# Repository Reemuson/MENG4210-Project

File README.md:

<h1 align="center">DREAM</h1>

<h2 align="center">Data Recording and Electrophysiological Acquisition Module</h2>

<p align="center" width="100%">
  
</p>

***

<p align="center">
  
&nbsp; &nbsp; &nbsp; &nbsp;
  
</p>

***

## SPECIFICATIONS

| Parameter | Value | 
| --- | --- |
| Dimensions | 100.0 × 60.0 mm |

***

## DIRECTORY STRUCTURE

    .
    ├─ Computations       # Misc calculations
    ├─ HTML               # HTML files for generated webpage
    ├─ Images             # Pictures and renders
    │
    ├─ kibot_resources    # External resources for KiBot
    │  ├─ colors          # Color theme for KiCad
    │  ├─ fonts           # Fonts used in the project
    │  ├─ scripts         # External scripts used with KiBot
    │  └─ templates       # Templates for KiBot generated reports
    │
    ├─ kibot_yaml         # KiBot YAML config files
    ├─ KiRI               # KiRI (PCB diff viewer) files
    │
    ├─ lib                # KiCad footprint and symbol libraries
    │  ├─ 3d_models       # Component 3D models
    │  ├─ lib_fp          # Footprint libraries
    │  └─ lib_sym         # Symbol libraries
    │
    ├─ Logos              # Logos
    │
    ├─ Manufacturing      # Assembly and fabrication documents
    │  ├─ Assembly        # Assembly documents (BoM, pos, notes)
    │  │
    │  └─ Fabrication     # Fabrication documents (ZIP, notes)
    │     ├─ Drill Tables # CSV drill tables
    │     └─ Gerbers      # Gerbers
    │
    ├─ Report             # Reports for ERC/DRC
    ├─ Schematic          # PDF of schematic
    ├─ Templates          # Title block templates
    ├─ Testing
    │  └─ Testpoints      # Testpoints tables      
    │
    └─ Variants           # Outputs for assembly variants

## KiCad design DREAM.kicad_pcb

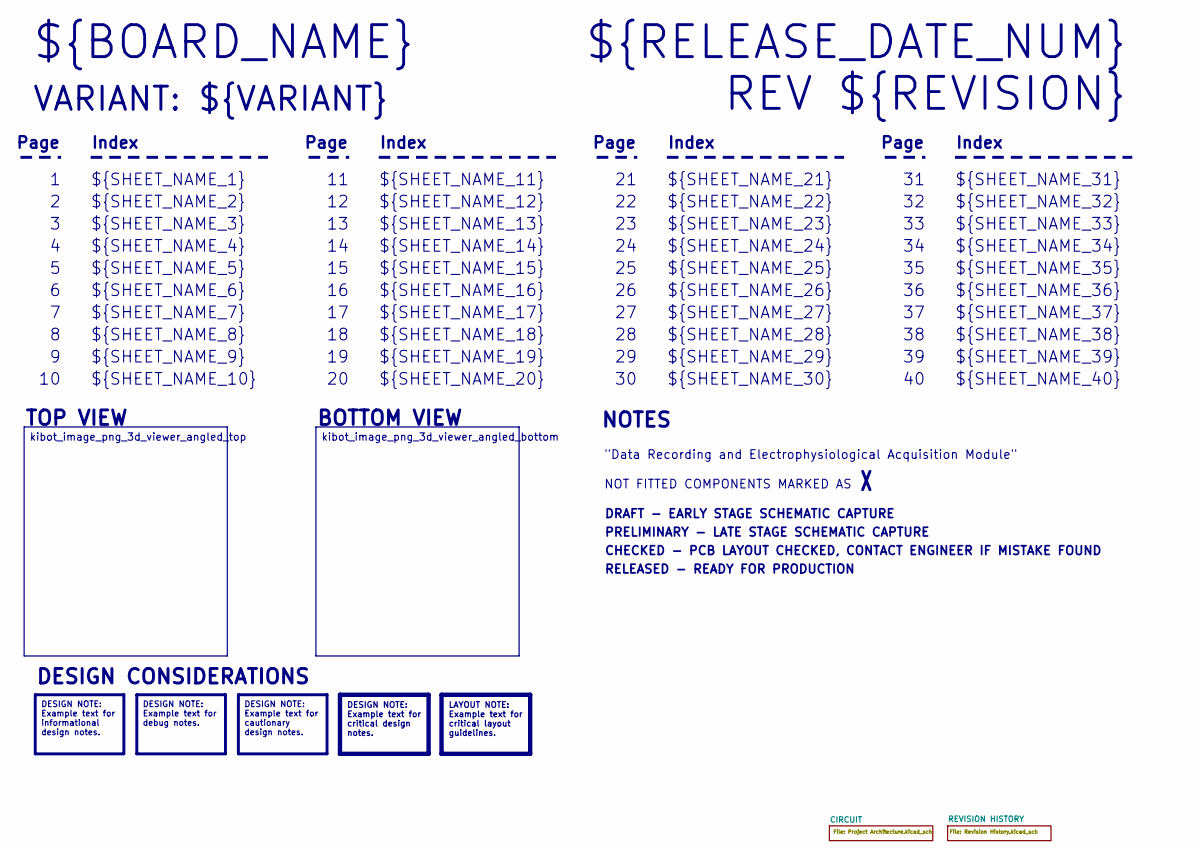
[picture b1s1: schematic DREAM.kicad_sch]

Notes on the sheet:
VARIANT: ${VARIANT}
RELEASED - READY FOR PRODUCTION
${SHEET_NAME_24}
Index
Page
PRELIMINARY - LATE STAGE SCHEMATIC CAPTURE
${SHEET_NAME_22}
DRAFT - EARLY STAGE SCHEMATIC CAPTURE
${SHEET_NAME_12}
${SHEET_NAME_8}
${SHEET_NAME_2}
${SHEET_NAME_5}
${SHEET_NAME_20}
${SHEET_NAME_23}
${RELEASE_DATE_NUM}
${SHEET_NAME_35}
NOT FITTED COMPONENTS MARKED AS
${SHEET_NAME_11}
${SHEET_NAME_6}
${SHEET_NAME_37}
${SHEET_NAME_26}
${SHEET_NAME_36}
REV ${REVISION}
${SHEET_NAME_15}
CHECKED - PCB LAYOUT CHECKED, CONTACT ENGINEER IF MISTAKE FOUND
BOTTOM VIEW
${SHEET_NAME_14}
${SHEET_NAME_21}
${SHEET_NAME_17}
${SHEET_NAME_18}
${SHEET_NAME_7}
${SHEET_NAME_31}
${BOARD_NAME}
NOTES
${SHEET_NAME_40}
${SHEET_NAME_39}
${SHEET_NAME_32}
${SHEET_NAME_1}
${SHEET_NAME_9}
${SHEET_NAME_38}

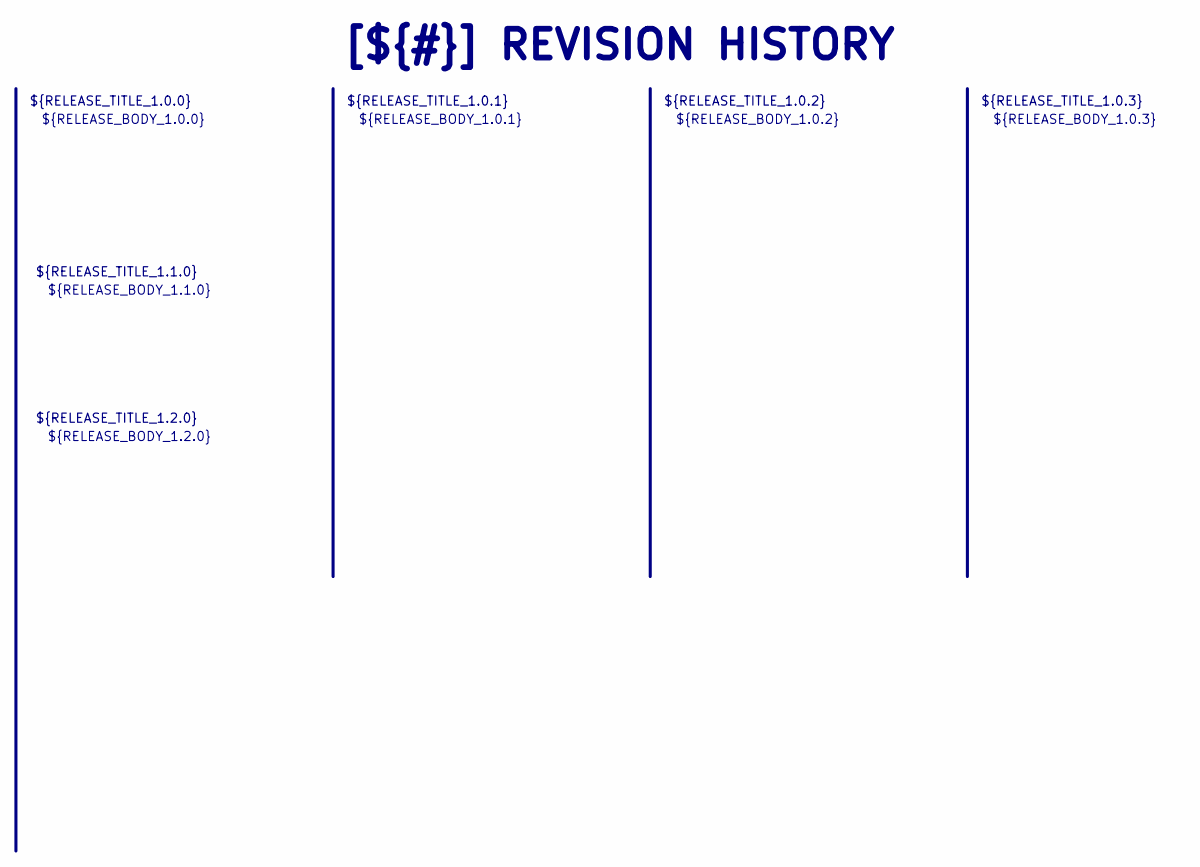
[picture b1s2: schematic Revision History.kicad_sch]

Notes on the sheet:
${RELEASE_BODY_1.0.3}
${RELEASE_TITLE_1.1.0}
[${#}] ${TITLE}
${RELEASE_BODY_1.0.0}
${RELEASE_TITLE_1.0.2}
${RELEASE_TITLE_1.2.0}
${RELEASE_BODY_1.0.2}
${RELEASE_BODY_1.0.1}
${RELEASE_BODY_1.1.0}
${RELEASE_BODY_1.2.0}
${RELEASE_TITLE_1.0.0}
${RELEASE_TITLE_1.0.1}
${RELEASE_TITLE_1.0.3}

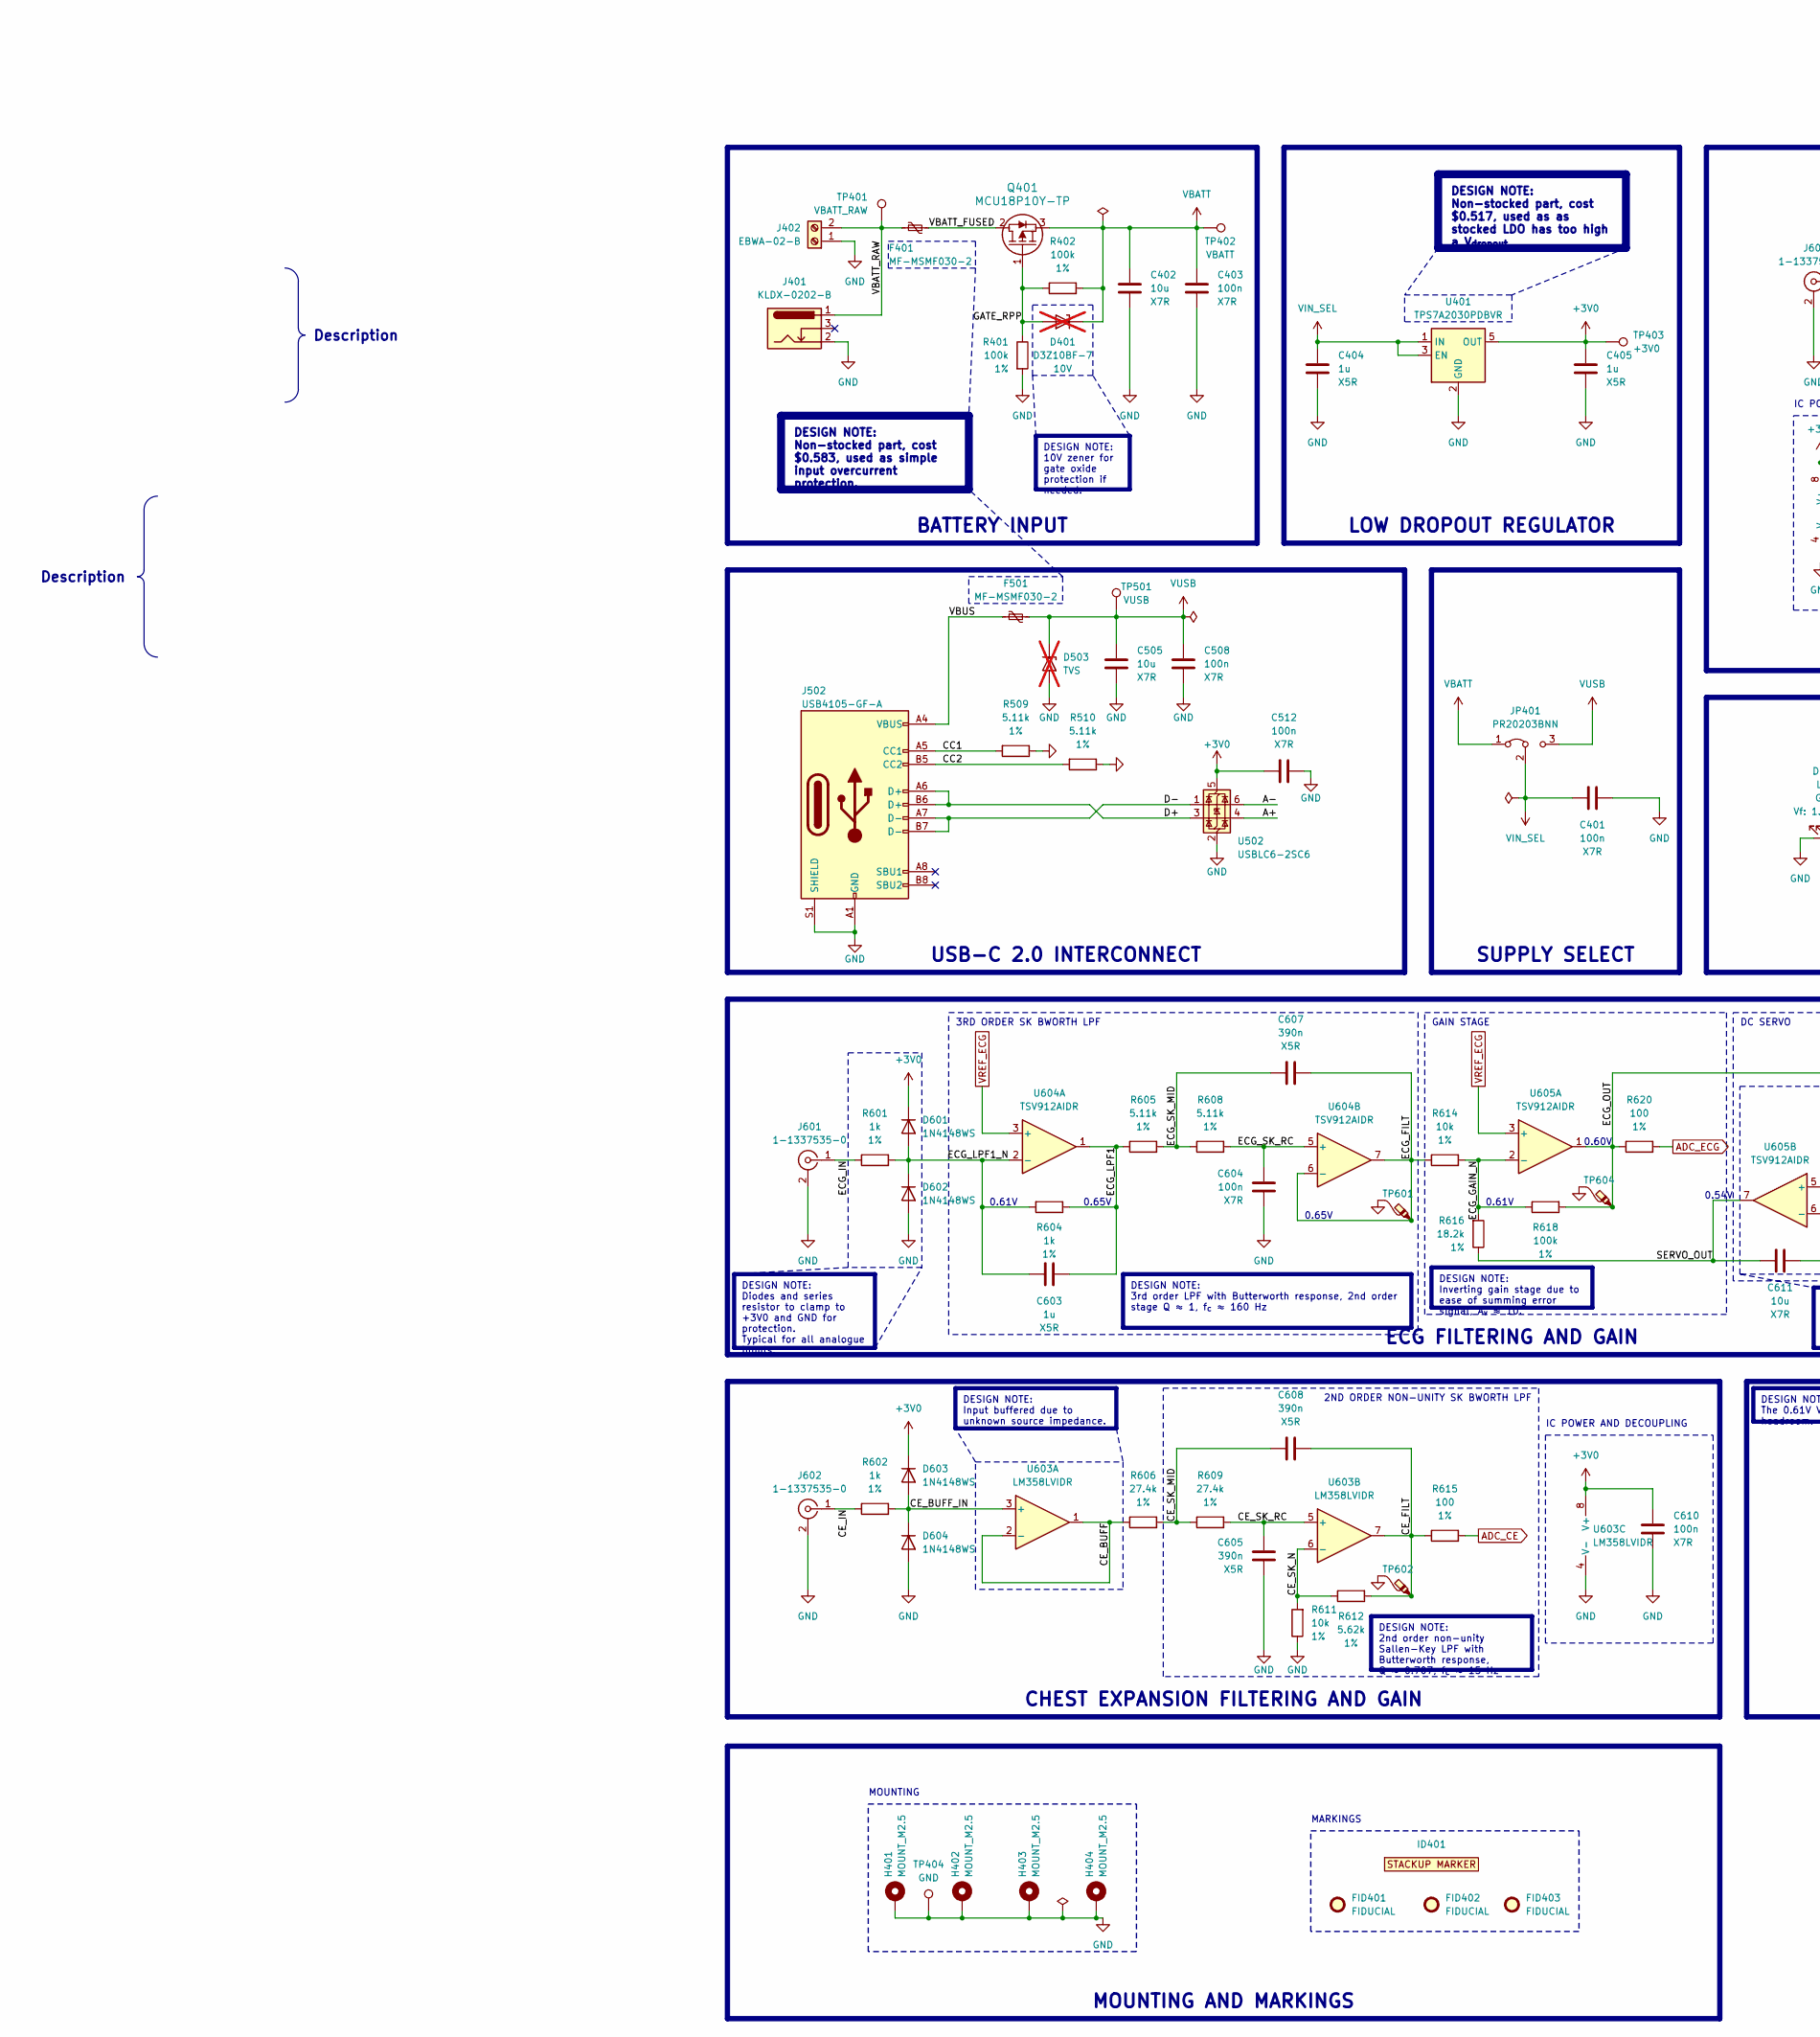
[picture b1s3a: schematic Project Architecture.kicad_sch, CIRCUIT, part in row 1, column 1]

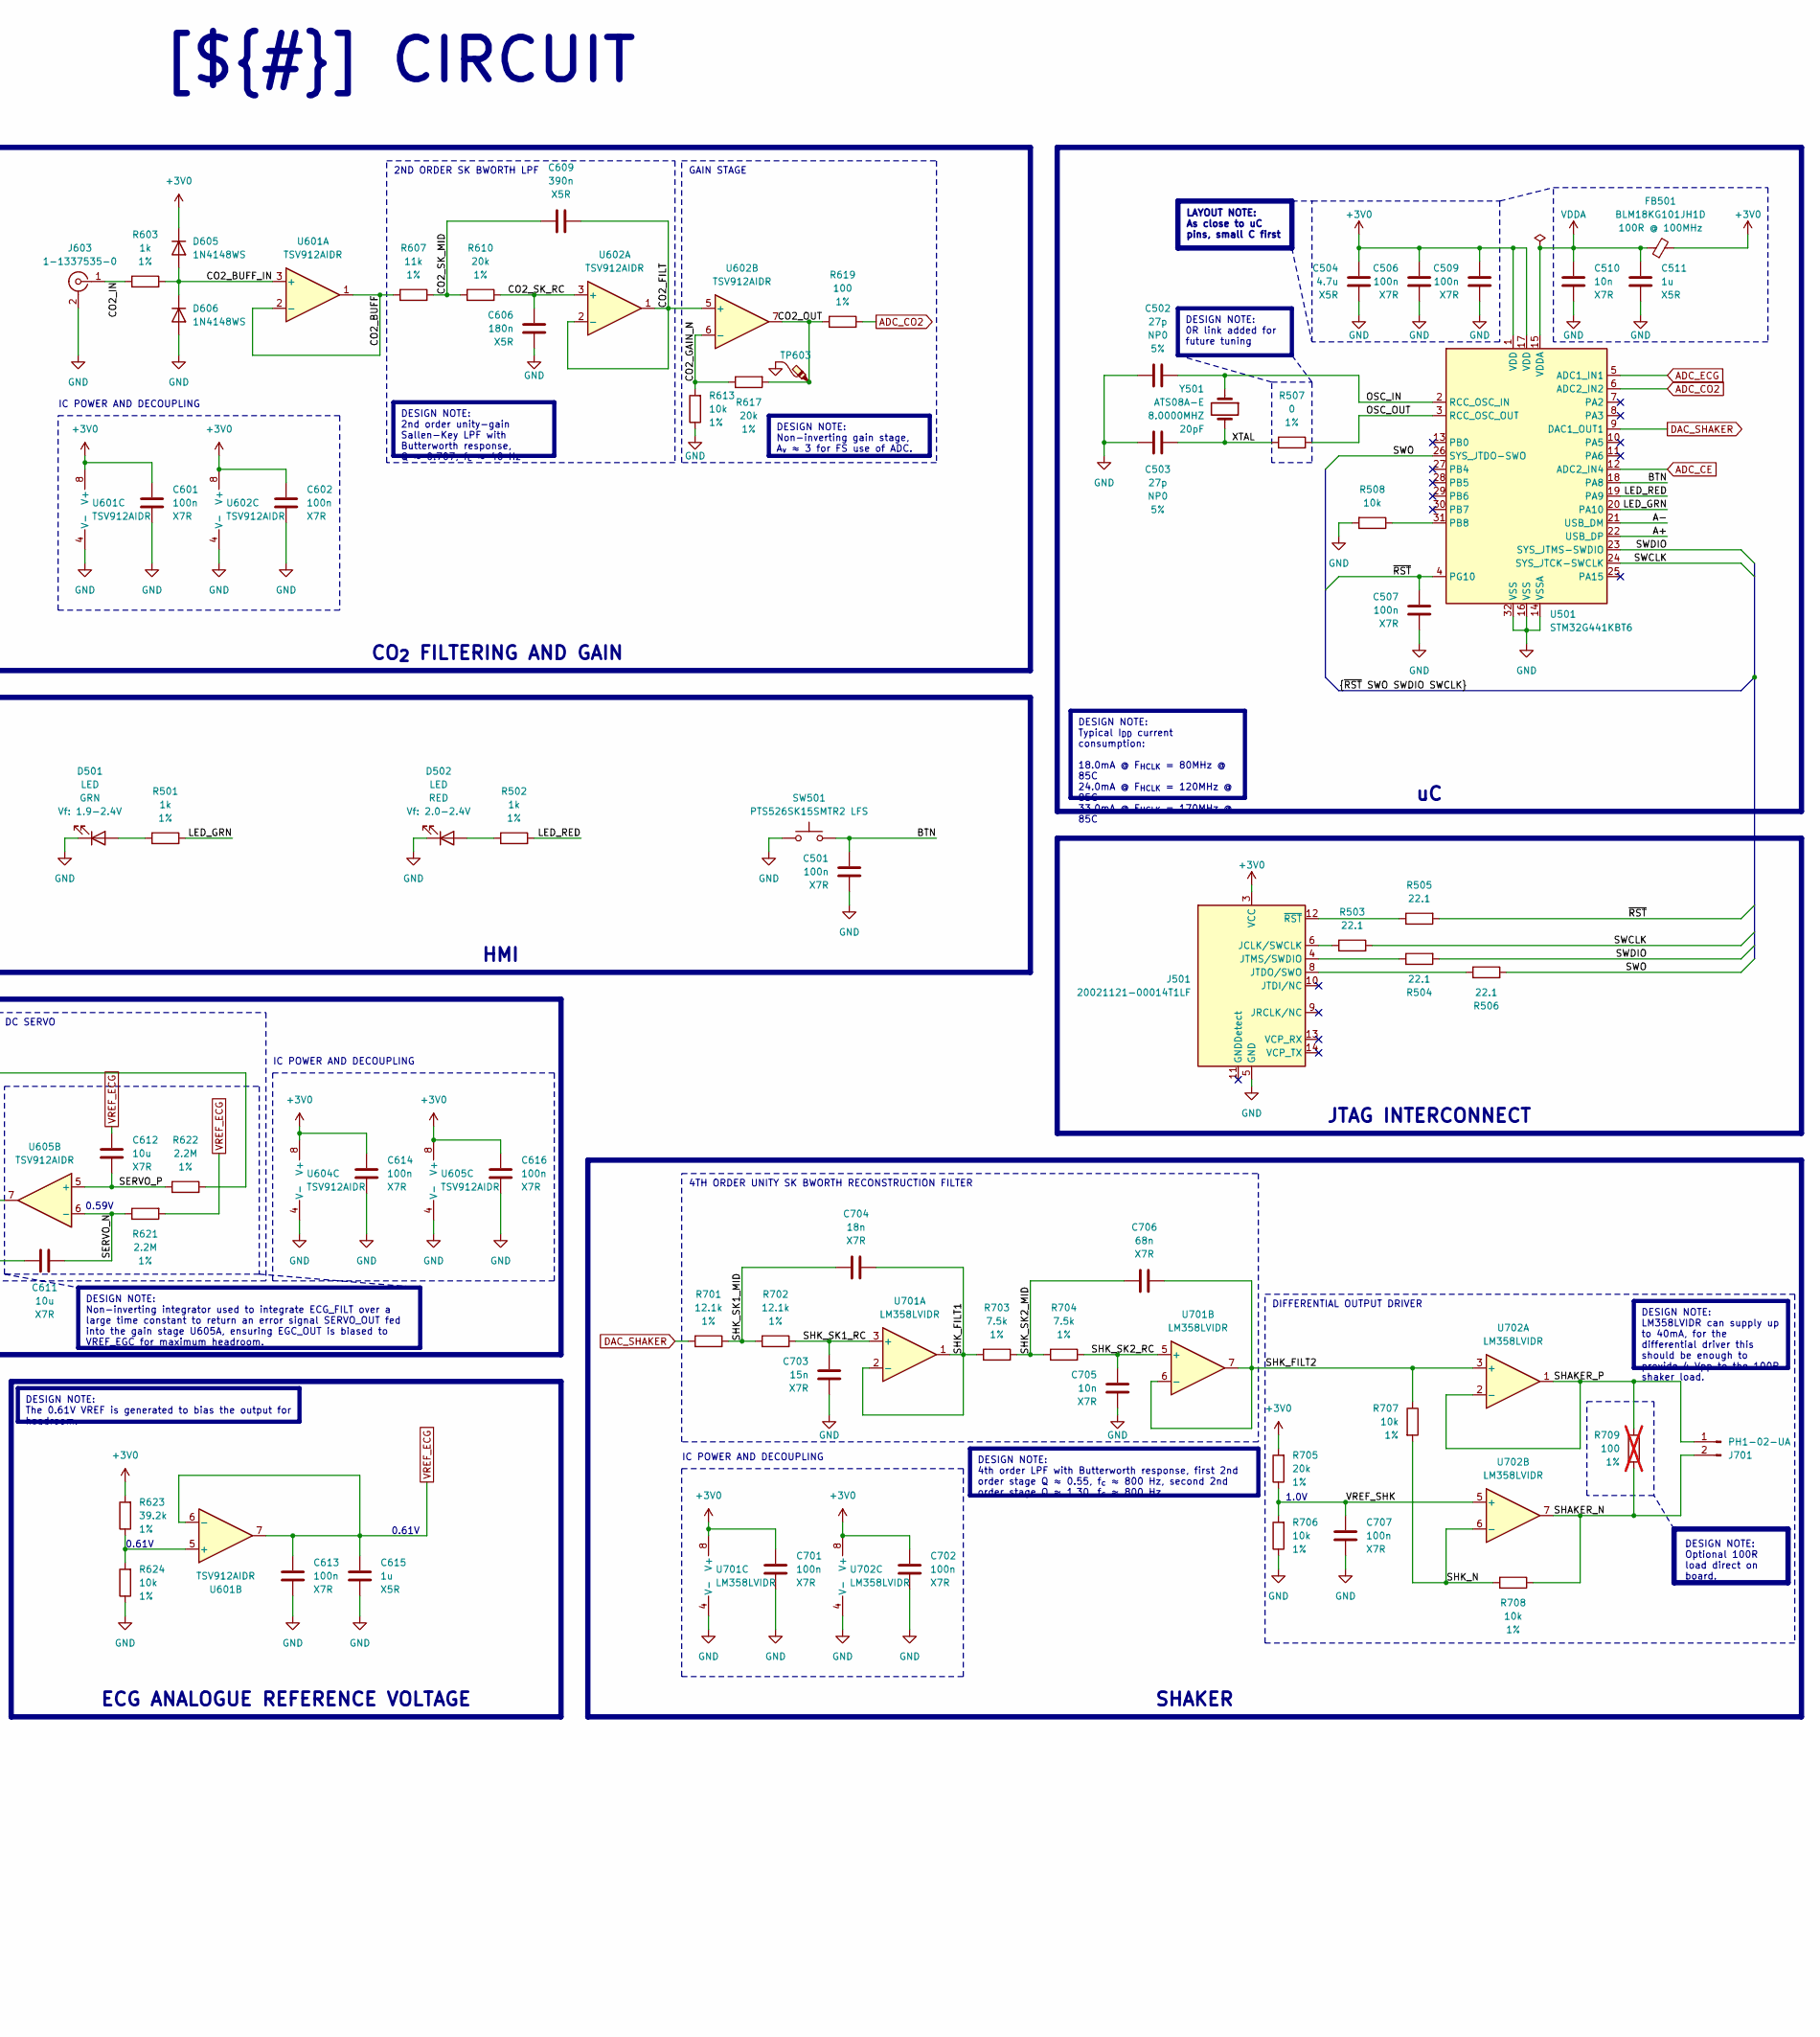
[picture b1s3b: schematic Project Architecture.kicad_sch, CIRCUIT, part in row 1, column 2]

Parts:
C401, C403, C501, C506, C507, C508, C509, C512, C601, C602, C604, C610, C613, C614, C616, C701, C702, C707: 100n; C_0603_1608Metric; Voltage_Rating 16V; Tolerance 10%; MPN C1608X7R1C104KT
C402, C505, C611, C612: 10u; C_0603_1608Metric; Voltage_Rating 6.3V; Tolerance 10%; MPN C1608X7R0J106KT
C404, C405, C511, C603, C615: 1u; C_0603_1608Metric; Voltage_Rating 6.3V; Tolerance 10%; MPN C1608X5R0J105KT
C502, C503: 27p; C_0603_1608Metric; Voltage_Rating 50V; Tolerance 5%; MPN C1608COG1H270JT
C504: 4.7u; C_0603_1608Metric; Voltage_Rating 6.3V; Tolerance 10%; MPN C1608X5R0J475MT
C510, C705: 10n; C_0603_1608Metric; Voltage_Rating 50V; Tolerance 10%; MPN C1608X7R1H103KT
C605, C607, C608, C609: 390n; C_0603_1608Metric; Voltage_Rating 10V; Tolerance 10%; MPN C1608X5R1A394KT
C606: 180n; C_0603_1608Metric; Voltage_Rating 10V; Tolerance 10%; MPN C1608X5R1A184KT
C703: 15n; C_0603_1608Metric; Voltage_Rating 50V; Tolerance 10%; MPN C1608X7R1H153KT
C704: 18n; C_0603_1608Metric; Voltage_Rating 16V; Tolerance 10%; MPN C1608X7R1C183KT
C706: 68n; C_0603_1608Metric; Voltage_Rating 16V; Tolerance 10%; MPN C1608X7R1C683KT
D401: D3Z10BF-7; D_SOD-323_HandSoldering; MPN D3Z10BF-7; not fitted
D501: LED; LED_0805_2012Metric; MPN LTST-C170KGKT
D502: LED; LED_0805_2012Metric; MPN LTST-C170KRKT
D503: TVS; D_SMB; not fitted
D601, D602, D603, D604, D605, D606: 1N4148WS; D_SOD-323_HandSoldering; MPN 1N4148WS
F401, F501: MF-MSMF030-2; R_1812_4532Metric; Voltage 30V; MPN Bourns Inc.
FB501: BLM18KG101JH1D; L_0603_1608Metric; MPN BLM18KG101JH1D
FID401, FID402, FID403: FIDUCIAL; Fiducial_1mm_Mask2mm
H401, H402, H403, H404: MOUNT_M2.5; MountingHole_2.7mm_M2.5_ISO7380_Pad
ID401: BOARD_STACKUP_MARKER; STACKUP_ID_2L
J401: KLDX-0202-B; BarrelJack_Kycon_KLDX-0202-xC_Horizontal; MPN KLDX-0202-B
J402: EBWA-02-B; TerminalBlock_Phoenix_MKDS-1-2-3.81_1x02_P3.81mm_Horizontal; MPN EBWA-02-B
J501: 20021121-00014T1LF; PinHeader_2x07_P1.27mm_Vertical_SMD; MPN 20021121-00014T1LF
J502: USB4105-GF-A; USB_C_Receptacle_GCT_USB4105-xx-A_16P_TopMnt_Horizontal; MPN USB4105-GF-A
J601, J602, J603: 1-1337535-0; BNC_TEConnectivity_1478204_Vertical; MPN 1-1337535-0
J701: PH1-02-UA; PinHeader_1x02_P2.54mm_Vertical
JP401: PR20203BNN; PinHeader_1x03_P2.54mm_Vertical; MPN PR20203BNN
Q401: MCU18P10Y-TP; DPAK_MCC; MPN MCU18P10Y-TP
R401, R402, R618: 100k; R_0603_1608Metric; Tolerance 1%
R501, R502, R601, R602, R603, R604: 1k; R_0603_1608Metric; Tolerance 1%
R503, R504, R505, R506: 22.1; R_0603_1608Metric; Tolerance 1%
R507: 0; R_0603_1608Metric; Tolerance 1%
R508, R611, R613, R614, R624, R706, R707, R708: 10k; R_0603_1608Metric; Tolerance 1%
R509, R510, R605, R608: 5.11k; R_0603_1608Metric; Tolerance 1%
R606, R609: 27.4k; R_0603_1608Metric; Tolerance 1%
R607: 11k; R_0603_1608Metric; Tolerance 1%
R610, R617, R705: 20k; R_0603_1608Metric; Tolerance 1%
R612: 5.62k; R_0603_1608Metric; Tolerance 1%
R615, R619, R620: 100; R_0603_1608Metric; Tolerance 1%
R616: 18.2k; R_0603_1608Metric; Tolerance 1%
R621, R622: 2.2M; R_0603_1608Metric; Tolerance 1%
R623: 39.2k; R_0603_1608Metric; Tolerance 1%
R701, R702: 12.1k; R_0603_1608Metric; Tolerance 1%
R703, R704: 7.5k; R_0603_1608Metric; Tolerance 1%
R709: 100; R_0603_1608Metric; Tolerance 1%; not fitted
SW501: PTS526SK15SMTR2 LFS; SW_SPST_PTS526xxxSMTR; MPN PTS526SK15SMTR2 LFS
TP401: VBATT_RAW; TestPoint_Pad_D1.0mm
TP402: VBATT; TestPoint_Pad_D1.0mm
TP403: +3V0; TestPoint_Pad_D1.0mm
TP404: GND; TestPoint_Pad_1.0x1.0mm
TP501: VUSB; TestPoint_Pad_D1.0mm
TP601, TP602, TP603, TP604: TestPoint_PMK_Probe; TestPoint_THTPad_PMK
U401: TPS7A2030PDBVR; SOT-23-5; MPN TPS7A2030PDBVR
U501: STM32G441KBT6; LQFP-32_7x7mm_P0.8mm; MPN STM32G441KBT6
U502: USBLC6-2SC6; SOT-23-6; MPN USBLC6-2SC6
U601, U602, U604, U605: TSV912AIDR; SOIC-8_3.9x4.9mm_P1.27mm; MPN TSV912AIDR
U603, U701, U702: LM358LVIDR; SOIC-8_3.9x4.9mm_P1.27mm; MPN LM358LVIDR
Y501: ATS08A-E; Crystal_HC49-4H_Vertical; MPN ATS08A-E

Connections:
+3V0: C405.2, C504.2, C506.2, C509.2, C512.2, C601.1, C602.1, C610.1, C614.1, C616.1, C701.1, C702.1, D601.1 (K), D603.1 (K), D605.1 (K), FB501.2, J501.3 (VCC), R623.2, R705.2, TP403.1, U401.5 (OUT), U501.1 (VDD), U501.17 (VDD), U502.5 (VBUS), U601.8 (V+), U602.8 (V+), U603.8 (V+), U604.8 (V+), U605.8 (V+), U701.8 (V+), U702.8 (V+)
/ARCHITECTURE/ANALOGUE INPUTS/ADC_CE: R615.2, U501.12 (ADC2_IN4)
/ARCHITECTURE/ANALOGUE INPUTS/ADC_CO2: R619.2, U501.6 (ADC2_IN2)
/ARCHITECTURE/ANALOGUE INPUTS/ADC_ECG: R620.2, U501.5 (ADC1_IN1)
/ARCHITECTURE/ANALOGUE INPUTS/CE_BUFF: R606.1, U603.1, U603.2 (-)
/ARCHITECTURE/ANALOGUE INPUTS/CE_BUFF_IN: D603.2 (A), D604.1 (K), R602.2, U603.3 (+)
/ARCHITECTURE/ANALOGUE INPUTS/CE_FILT: C608.1, R612.2, R615.1, TP602.1, U603.7
/ARCHITECTURE/ANALOGUE INPUTS/CE_IN: J602.1 (In), R602.1
/ARCHITECTURE/ANALOGUE INPUTS/CE_SK_MID: C608.2, R606.2, R609.1
/ARCHITECTURE/ANALOGUE INPUTS/CE_SK_N: R611.2, R612.1, U603.6 (-)
/ARCHITECTURE/ANALOGUE INPUTS/CE_SK_RC: C605.1, R609.2, U603.5 (+)
/ARCHITECTURE/ANALOGUE INPUTS/CO2_BUFF: R607.1, U601.1, U601.2 (-)
/ARCHITECTURE/ANALOGUE INPUTS/CO2_BUFF_IN: D605.2 (A), D606.1 (K), R603.2, U601.3 (+)
/ARCHITECTURE/ANALOGUE INPUTS/CO2_FILT: C609.1, U602.1, U602.2 (-), U602.5 (+)
/ARCHITECTURE/ANALOGUE INPUTS/CO2_GAIN_N: R613.2, R617.1, U602.6 (-)
/ARCHITECTURE/ANALOGUE INPUTS/CO2_IN: J603.1 (In), R603.1
/ARCHITECTURE/ANALOGUE INPUTS/CO2_OUT: R617.2, R619.1, TP603.1, U602.7
/ARCHITECTURE/ANALOGUE INPUTS/CO2_SK_MID: C609.2, R607.2, R610.1
/ARCHITECTURE/ANALOGUE INPUTS/CO2_SK_RC: C606.1, R610.2, U602.3 (+)
/ARCHITECTURE/ANALOGUE INPUTS/ECG_FILT: C607.1, R614.1, TP601.1, U604.6 (-), U604.7
/ARCHITECTURE/ANALOGUE INPUTS/ECG_GAIN_N: R614.2, R616.2, R618.1, U605.2 (-)
/ARCHITECTURE/ANALOGUE INPUTS/ECG_IN: J601.1 (In), R601.1
/ARCHITECTURE/ANALOGUE INPUTS/ECG_LPF1: C603.1, R604.1, R605.1, U604.1
/ARCHITECTURE/ANALOGUE INPUTS/ECG_LPF1_N: C603.2, D601.2 (A), D602.1 (K), R601.2, R604.2, U604.2 (-)
/ARCHITECTURE/ANALOGUE INPUTS/ECG_OUT: R618.2, R620.1, R622.2, TP604.1, U605.1
/ARCHITECTURE/ANALOGUE INPUTS/ECG_SK_MID: C607.2, R605.2, R608.1
/ARCHITECTURE/ANALOGUE INPUTS/ECG_SK_RC: C604.1, R608.2, U604.5 (+)
/ARCHITECTURE/ANALOGUE INPUTS/SERVO_N: C611.1, R621.1, U605.6 (-)
/ARCHITECTURE/ANALOGUE INPUTS/SERVO_OUT: C611.2, R616.1, U605.7
/ARCHITECTURE/ANALOGUE INPUTS/SERVO_P: C612.2, R622.1, U605.5 (+)
/ARCHITECTURE/ANALOGUE OUTPUTS/DAC_SHAKER: R701.1, U501.9 (DAC1_OUT1)
/ARCHITECTURE/ANALOGUE OUTPUTS/SHAKER_N: J701.2, R708.1, R709.2, U702.7
/ARCHITECTURE/ANALOGUE OUTPUTS/SHAKER_P: J701.1, R709.1, U702.1, U702.2 (-)
/ARCHITECTURE/ANALOGUE OUTPUTS/SHK_FILT1: C704.1, R703.1, U701.1, U701.2 (-)
/ARCHITECTURE/ANALOGUE OUTPUTS/SHK_FILT2: C706.1, R707.1, U701.6 (-), U701.7, U702.3 (+)
/ARCHITECTURE/ANALOGUE OUTPUTS/SHK_N: R707.2, R708.2, U702.6 (-)
/ARCHITECTURE/ANALOGUE OUTPUTS/SHK_SK1_MID: C704.2, R701.2, R702.1
/ARCHITECTURE/ANALOGUE OUTPUTS/SHK_SK1_RC: C703.1, R702.2, U701.3 (+)
/ARCHITECTURE/ANALOGUE OUTPUTS/SHK_SK2_MID: C706.2, R703.2, R704.1
/ARCHITECTURE/ANALOGUE OUTPUTS/SHK_SK2_RC: C705.1, R704.2, U701.5 (+)
/ARCHITECTURE/ANALOGUE OUTPUTS/VREF_SHK: C707.1, R705.1, R706.2, U702.5 (+)
/ARCHITECTURE/DIGITAL AND HMI/A+: U501.22 (USB_DP), U502.4 (I/O2)
/ARCHITECTURE/DIGITAL AND HMI/A-: U501.21 (USB_DM), U502.6 (I/O1)
/ARCHITECTURE/DIGITAL AND HMI/BTN: C501.2, SW501.2, U501.18 (PA8)
/ARCHITECTURE/DIGITAL AND HMI/CC1: J502.A5 (CC1), R509.2
/ARCHITECTURE/DIGITAL AND HMI/CC2: J502.B5 (CC2), R510.2
/ARCHITECTURE/DIGITAL AND HMI/D+: J502.A6 (D+), J502.B6 (D+), U502.3 (I/O2)
/ARCHITECTURE/DIGITAL AND HMI/D-: J502.A7 (D-), J502.B7 (D-), U502.1 (I/O1)
/ARCHITECTURE/DIGITAL AND HMI/LED_GRN: R501.2, U501.20 (PA10)
/ARCHITECTURE/DIGITAL AND HMI/LED_RED: R502.2, U501.19 (PA9)
/ARCHITECTURE/DIGITAL AND HMI/OSC_IN: C502.2, U501.2 (RCC_OSC_IN), Y501.1
/ARCHITECTURE/DIGITAL AND HMI/OSC_OUT: R507.2, U501.3 (RCC_OSC_OUT)
/ARCHITECTURE/DIGITAL AND HMI/SWCLK: R503.2, U501.24 (SYS_JTCK-SWCLK)
/ARCHITECTURE/DIGITAL AND HMI/SWDIO: R504.2, U501.23 (SYS_JTMS-SWDIO)
/ARCHITECTURE/DIGITAL AND HMI/SWO: R506.2, U501.26 (SYS_JTDO-SWO)
/ARCHITECTURE/DIGITAL AND HMI/VBUS: F501.1, J502.A4 (VBUS), J502.A9 (VBUS), J502.B4 (VBUS), J502.B9 (VBUS)
/ARCHITECTURE/DIGITAL AND HMI/VDDA: C510.2, C511.2, FB501.1, U501.15 (VDDA)
/ARCHITECTURE/DIGITAL AND HMI/XTAL: C503.1, R507.1, Y501.2
/ARCHITECTURE/DIGITAL AND HMI/~RST: C507.2, R505.2, U501.4 (PG10)
/ARCHITECTURE/POWER/GATE_RPP: D401.2 (A), Q401.1, R401.1, R402.1
/ARCHITECTURE/POWER/VBATT_FUSED: F401.2, Q401.2
/ARCHITECTURE/POWER/VBATT_RAW: F401.1, J401.1, J402.2, TP401.1
GND: C401.2, C402.2, C403.2, C404.1, C405.1, C501.1, C502.1, C503.2, C504.1, C505.2, C506.1, C507.1, C508.2, C509.1, C510.1, C511.1, C512.1, C601.2, C602.2, C604.2, C605.2, C606.2, C610.2, C613.2, C614.2, C615.1, C616.2, C701.2, C702.2, C703.2, C705.2, C707.2, D501.1 (K), D502.1 (K), D503.2 (A2), D602.2 (A), D604.2 (A), D606.2 (A), H401.1, H402.1, H403.1, H404.1, J401.2, J402.1, J501.5 (GND), J501.7 (GND), J502.A1 (GND), J502.A12 (GND), J502.B1 (GND), J502.B12 (GND), J502.S1 (SHIELD), J601.2 (Ext), J602.2 (Ext), J603.2 (Ext), R401.2, R508.2, R509.1, R510.1, R611.1, R613.1, R624.1, R706.1, SW501.1, TP404.1, TP601.2, TP602.2, TP603.2, TP604.2, U401.2 (GND), U501.14 (VSSA), U501.16 (VSS), U501.32 (VSS), U502.2 (GND), U601.4 (V-), U602.4 (V-), U603.4 (V-), U604.4 (V-), U605.4 (V-), U701.4 (V-), U702.4 (V-)
unnamed: D501.2 (A), R501.1
unnamed: D502.2 (A), R502.1
unnamed: J501.6 (JCLK/SWCLK), R503.1
unnamed: J501.8 (JTDO/SWO), R506.1
unnamed: J501.4 (JTMS/SWDIO), R504.1
unnamed: J501.12 (~RST), R505.1
unnamed: R508.1, U501.31 (PB8)
unnamed: R623.1, R624.2, U601.5 (+)
VBATT: C402.1, C403.1, D401.1 (K), JP401.1 (A), Q401.3, R402.2, TP402.1
VIN_SEL: C401.1, C404.2, JP401.2 (C), U401.1 (IN), U401.3 (EN)
VREF_ECG: C612.1, C613.1, C615.2, R621.2, U601.6 (-), U601.7, U604.3 (+), U605.3 (+)
VUSB: C505.1, C508.1, D503.1 (A1), F501.2, JP401.3 (B), TP501.1

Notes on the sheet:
MOUNTING
IC POWER AND DECOUPLING
MARKINGS
0.60V
0.61V
3RD ORDER SK BWORTH LPF
DC SERVO
0.59V
0.65V
0.54V
GAIN STAGE
2ND ORDER SK BWORTH LPF
1.0V
4TH ORDER UNITY SK BWORTH RECONSTRUCTION FILTER
2ND ORDER NON-UNITY SK BWORTH LPF
0.61V
DIFFERENTIAL OUTPUT DRIVER
HMI
ECG ANALOGUE REFERENCE VOLTAGE
DESIGN NOTE: 10V zener for gate oxide protection if needed.
DESIGN NOTE: Non-inverting integrator used to integrate ECG_FILT over a large time constant to return an error signal SERVO_OUT fed into the gain stage U605A, ensuring EGC_OUT is biased to VREF_EGC for maximum headroom.
LAYOUT NOTE: As close to uC pins, small C first
ECG FILTERING AND GAIN
DESIGN NOTE: 2nd order unity-gain Sallen-Key LPF with Butterworth response, Q ≈ 0.707, f_{c} ≈ 40 Hz
DESIGN NOTE: Input buffered due to unknown source impedance.
MOUNTING AND MARKINGS
DESIGN NOTE: LM358LVIDR can supply up to 40mA, for the differential driver this should be enough to provide 4 Vpp to the 100R shaker load.
SUPPLY SELECT
DESIGN NOTE: The 0.61V VREF is generated to bias the output for headroom.
JTAG INTERCONNECT
LOW DROPOUT REGULATOR
DESIGN NOTE: Typical I_{DD} current consumption: 18.0mA @ F_{HCLK} = 80MHz @ 85C 24.0mA @ F_{HCLK} = 120MHz @ 85C 33.0mA @ F_{HCLK} = 170MHz @ 85C
DESIGN NOTE: Optional 100R load direct on board.
SHAKER
Description
DESIGN NOTE: Non-stocked part, cost $0.517, used as as stocked LDO has too high a V_{dropout}
DESIGN NOTE: Non-stocked part, cost $0.583, used as simple input overcurrent protection.
DESIGN NOTE: Non-inverting gain stage, A_{v} ≈ 3 for FS use of ADC.
DESIGN NOTE: Diodes and series resistor to clamp to +3V0 and GND for protection. Typical for all analogue inputs.
CHEST EXPANSION FILTERING AND GAIN

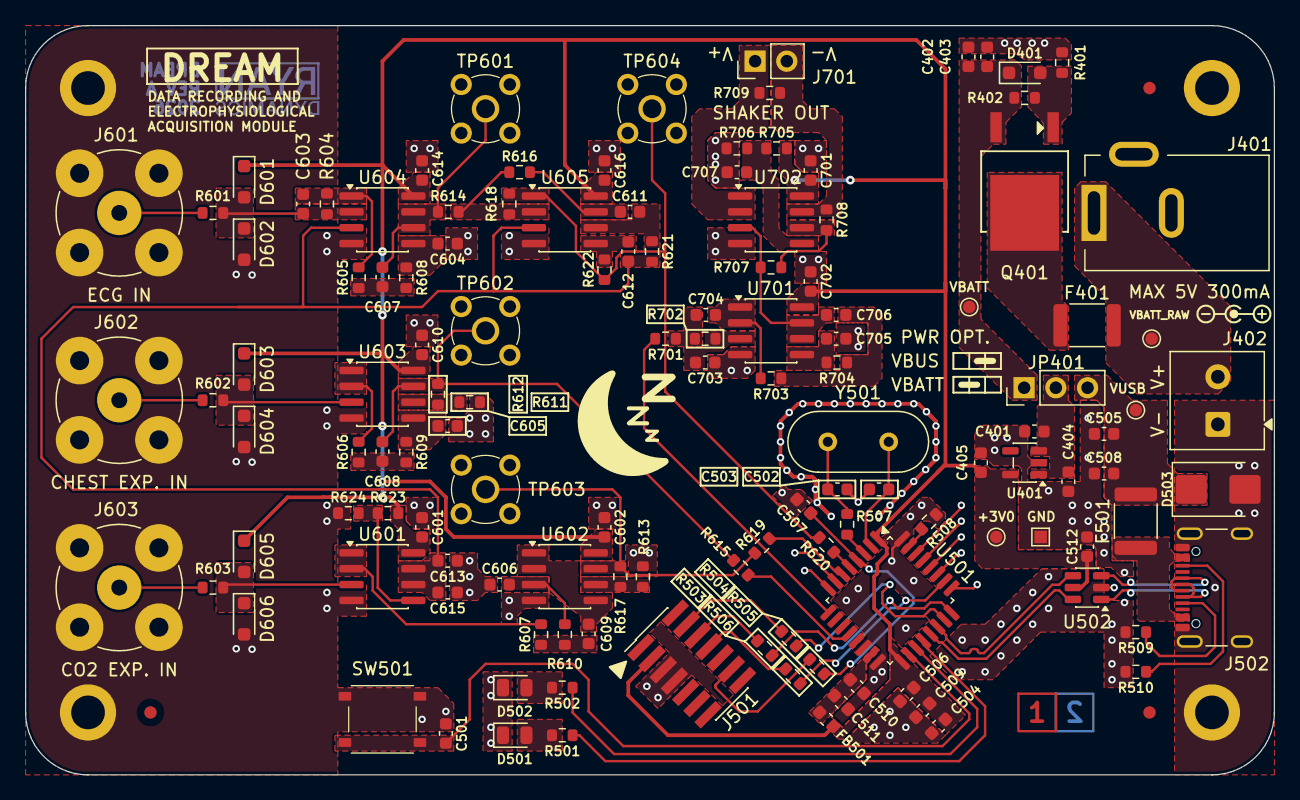
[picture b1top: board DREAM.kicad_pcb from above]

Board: 2 copper layers, 100.0 x 60.0 mm, 137 parts (0 on the bottom side), 75 nets.

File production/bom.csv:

Designator,Footprint,Quantity,Value,LCSC Part #
"C401, C403, C501, C506, C507, C508, C509, C512, C601, C602, C604, C610, C613, C614, C616, C701, C702, C707",0603,18,100n,C1608X7R1C104KT
"C402, C505, C611, C612",0603,4,10u,C1608X7R0J106KT
"C404, C405, C511, C603, C615",0603,5,1u,C1608X5R0J105KT
"C502, C503",0603,2,27p,C1608COG1H270JT 
C504,0603,1,4.7u,C1608X5R0J475MT
"C510, C705",0603,2,10n,C1608X7R1H103KT
"C605, C607, C608, C609",0603,4,390n,C1608X5R1A394KT
C606,0603,1,180n,C1608X5R1A184KT
C703,0603,1,15n,C1608X7R1H153KT
C704,0603,1,18n,C1608X7R1C183KT
C706,0603,1,68n,C1608X7R1C683KT
D401,D_SOD-323_HandSoldering,1,D3Z10BF-7,D3Z10BF-7
D501,0805,1,LED,LTST-C170KGKT
D502,0805,1,LED,LTST-C170KRKT
"D601, D602, D603, D604, D605, D606",D_SOD-323_HandSoldering,6,1N4148WS,1N4148WS
"F401, F501",1812,2,MF-MSMF030-2,Bourns Inc.
FB501,0603,1,MH1608-601Y,MH1608-601Y
J401,BarrelJack_Kycon_KLDX-0202-xC_Horizontal,1,KLDX-0202-B,KLDX-0202-B
J402,TerminalBlock_Phoenix_MKDS-1-2-3.81_1x02_P3.81mm_Horizontal,1,EBWA-02-B,EBWA-02-B
J501,PinHeader_2x07_P1.27mm_Vertical_SMD,1,Conn_ST_STDC14,
J502,USB_C_Receptacle_GCT_USB4105-xx-A_16P_TopMnt_Horizontal,1,USB4105-GF-A,USB4105-GF-A
"J601, J602, J603",BNC_TEConnectivity_1478204_Vertical,3,1-1337535-0,1-1337535-0
J701,PinHeader_1x02_P2.54mm_Vertical,1,PH1-02-UA,
Q401,DPAK_MCC,1,MCU18P10Y-TP,MCU18P10Y-TP
"R401, R402",0603,2,100k,
"R501, R502, R601, R602, R603, R604",0603,6,1k,
"R503, R504, R505, R506",0603,4,22.1,
R507,0603,1,0,
"R508, R611, R613, R614, R624, R706, R707, R708",0603,8,10k,
"R509, R510, R605, R608",0603,4,5.11k,
"R606, R609",0603,2,27.4k,
R607,0603,1,11k,
"R610, R617, R705",0603,3,20k,
R612,0603,1,5.62k,
"R615, R619, R620, R709",0603,4,100,
R616,0603,1,18.2k,
R618,0603,1,249k,
"R621, R622",0603,2,2.2M,
R623,0603,1,39.2k,
"R701, R702",0603,2,12.1k,
"R703, R704",0603,2,7.5k,
SW501,SW_SPST_PTS526xxxSMTR,1,PTS526SK15SMTR2 LFS,PTS526SK15SMTR2 LFS
U401,SOT-23-5,1,TPS7A2030PDBVR,TPS7A2030PDBVR
U501,LQFP-32_7x7mm_P0.8mm,1,STM32G441KBT6,STM32G441KBT6
U502,SOT-23-6,1,USBLC6-2SC6,USBLC6-2SC6
"U601, U602, U604, U605",SOIC-8_3.9x4.9mm_P1.27mm,4,TSV912AIDR,TSV912AIDR
"U603, U701, U702",SOIC-8_3.9x4.9mm_P1.27mm,3,LM358LVIDR,LM358LVIDR
Y501,Crystal_HC49-4H_Vertical,1,ATS08A-E,ATS08A-E

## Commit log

2026-04-06 Initial main empty commit
2026-04-12 feat: schematic capture and preliminary PCB layout
2026-04-12 Update Outputs
2026-04-12 fix: pdf size
2026-04-14 feat: checked REV A
2026-04-14 fix: schem and fab document
2026-04-14 fix: schematic note wording
2026-04-14 Update CHANGELOG
2026-04-14 Update Outputs (release)
2026-04-14 fix: ground under XTAL, untent vias, production files
2026-04-14 fix: net naming, NC STM32 pins, silkscreen, pin 1 indicator
2026-04-14 fix: improved crystal oscillator layout
2026-04-14 fix: add ground pour under uC
2026-05-09 fix: circuit schem as one sheet
2026-05-09 feat: board image
2026-05-09 fix: erc
2026-05-09 chore: fix changelog error from gh actions
